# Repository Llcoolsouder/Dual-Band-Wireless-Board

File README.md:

# Dual-Band-Wireless-Board

This board is a proof of concept of a system which will allow seamless wireless data transfer and wireless power simultanneously; even when antennae are extremely close together.

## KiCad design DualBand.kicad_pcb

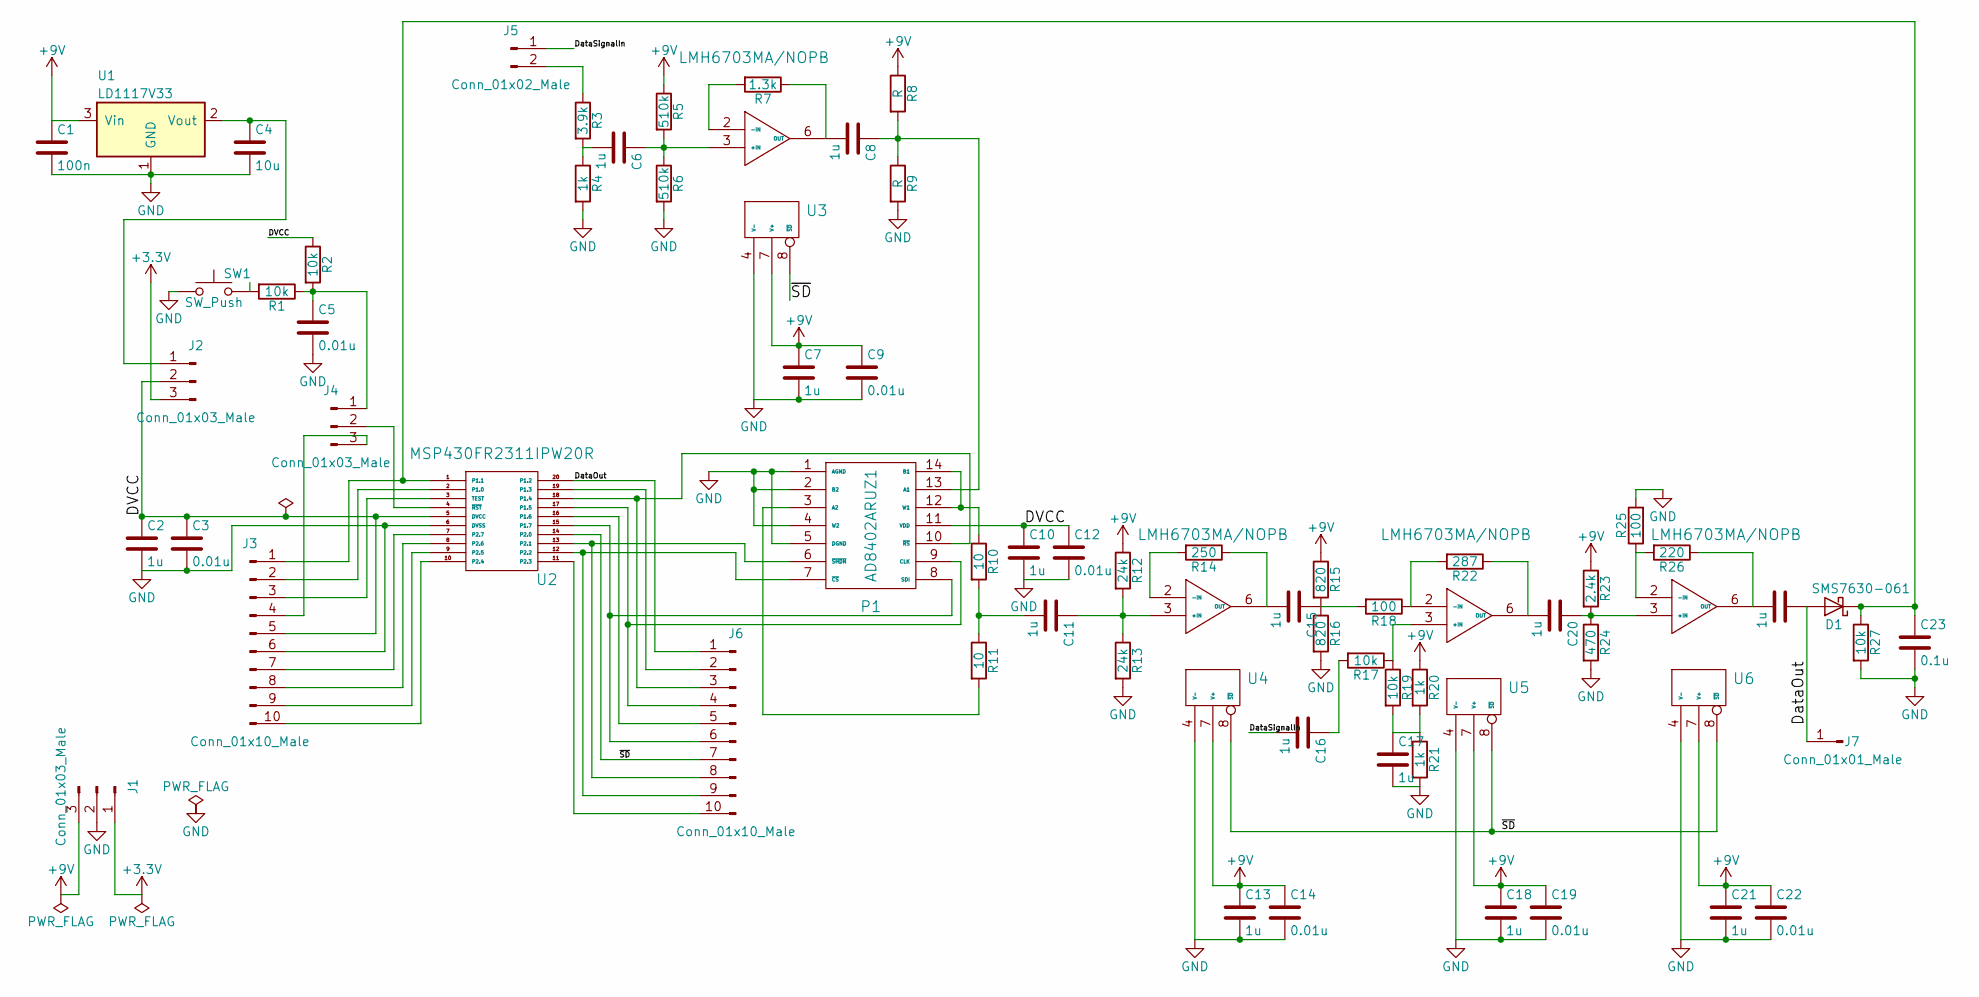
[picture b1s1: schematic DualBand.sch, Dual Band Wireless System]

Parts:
C1: 100n; C_0603
C2, C6, C7, C8, C10, C11, C13, C15, C16, C17, C18, C20, C21, C24: 1u; C_0603
C3, C5, C9, C12, C14, C19, C22: 0.01u; C_0603
C4: 10u; C_0603
C23: 0.1u; C_0603
D1: SMS7630-061; D_0201
J1, J2, J4: Conn_01x03_Male; Pin_Header_Straight_1x03_Pitch2.54mm
J3, J6: Conn_01x10_Male; Pin_Header_Straight_1x10_Pitch2.54mm
J5: Conn_01x02_Male; Pin_Header_Straight_1x02_Pitch2.54mm
J7: Conn_01x01_Male; Pin_Header_Straight_1x01_Pitch2.54mm
P1: AD8402ARUZ1; TSSOP-14_4.4x5mm_Pitch0.65mm
R1, R2, R17, R19, R27: 10k; R_0603
R3: 3.9k; R_0603
R4, R20, R21: 1k; R_0603
R5, R6: 510k; R_0603
R7: 1.3k; R_0603
R8, R9: R; R_0603
R10, R11: 10; R_0603
R12, R13: 24k; R_0603
R14: 250; R_0603
R15, R16: 820; R_0603
R18, R25: 100; R_0603
R22: 287; R_0603
R23: 2.4k; R_0603
R24: 470; R_0603
R26: 220; R_0603
SW1: SW_Push; FSM2JSMAATR
U1: LD1117V33; TO-220-3_Vertical
U2: MSP430FR2311IPW20R; TSSOP-20_4.4x6.5mm_Pitch0.65mm
U3, U4, U5, U6: LMH6703MA/NOPB; SOIC-8_3.9x4.9mm_Pitch1.27mm

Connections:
+3V3: J1.1, J2.3
+9V: C1.1, C7.1, C9.1, C13.1, C14.1, C18.1, C19.1, C21.1, C22.1, J1.3, R5.1, R8.1, R12.1, R15.1, R20.1, R23.1, U1.3 (Vin), U3.7 (V+), U4.7 (V+), U5.7 (V+), U6.7 (V+)
/DVCC: C2.1, C3.1, C10.1, C12.1, J2.2, J3.5, P1.11 (VDD), R2.1, U2.5 (DVCC)
/DataOut: C24.1, D1.2 (A), J6.1, J7.1, U2.20 (P1.2)
/DataSignalIn: C16.2, J5.1
/~SD: J6.7, U2.14 (P2.0), U3.8 (~SD), U4.8 (~SD), U5.8 (~SD), U6.8 (~SD)
GND: C1.2, C2.2, C3.2, C4.2, C5.2, C7.2, C9.2, C10.2, C12.2, C13.2, C14.2, C17.2, C18.2, C19.2, C21.2, C22.2, C23.2, J1.2, J3.6, P1.1 (AGND), P1.2 (B2), P1.4 (W2), P1.5 (DGND), R4.2, R6.2, R9.2, R13.2, R16.2, R21.2, R24.2, R25.2, R27.2, SW1.1, U1.1 (GND), U2.6 (DVSS), U3.4 (V-), U4.4 (V-), U5.4 (V-), U6.4 (V-)
unnamed: C4.1, J2.1, U1.2 (Vout)
unnamed: C5.1, J4.1, R1.1, R2.2
unnamed: C6.1, R5.2, R6.1, U3.3 (+IN)
unnamed: C6.2, R3.2, R4.1
unnamed: C8.1, P1.13 (A1), R8.2, R9.1
unnamed: C8.2, R7.1, U3.6 (OUT)
unnamed: C11.1, R12.2, R13.1, U4.3 (+IN)
unnamed: C11.2, R10.2, R11.1
unnamed: C15.1, R15.2, R16.1, R18.2
unnamed: C15.2, R14.1, U4.6 (OUT)
unnamed: C16.1, R17.2
unnamed: C17.1, R19.2, R20.2, R21.1
unnamed: C20.1, R23.2, R24.1, U6.3 (+IN)
unnamed: C20.2, R22.1, U5.6 (OUT)
unnamed: C23.1, D1.1 (K), J3.1, R27.1, U2.1 (P1.1)
unnamed: C24.2, R26.1, U6.6 (OUT)
unnamed: J3.2, U2.2 (P1.0)
unnamed: J3.3, U2.3 (TEST)
unnamed: J3.4, J4.3
unnamed: J3.7, U2.7 (P2.7)
unnamed: J3.8, U2.8 (P2.6)
unnamed: J3.9, U2.9 (P2.5)
unnamed: J3.10, U2.10 (P2.4)
unnamed: J4.2, U2.4 (~RST)
unnamed: J5.2, R3.1
unnamed: J6.2, U2.19 (P1.3)
unnamed: J6.3, P1.10 (~RS), U2.18 (P1.4)
unnamed: J6.4, P1.9 (CLK), U2.17 (P1.5)
unnamed: J6.5, U2.16 (P1.6)
unnamed: J6.6, P1.8 (SDI), U2.15 (P1.7)
unnamed: J6.8, P1.6 (~SHDN), U2.13 (P2.1)
unnamed: J6.9, P1.7 (~CS), U2.12 (P2.2)
unnamed: J6.10, U2.11 (P2.3)
unnamed: P1.3 (A2), R11.2
unnamed: P1.12 (W1), P1.14 (B1), R10.1
unnamed: R1.2, SW1.2
unnamed: R7.2, U3.2 (-IN)
unnamed: R14.2, U4.2 (-IN)
unnamed: R17.1, R19.1, U5.3 (+IN)
unnamed: R18.1, R22.2, U5.2 (-IN)
unnamed: R25.1, R26.2, U6.2 (-IN)

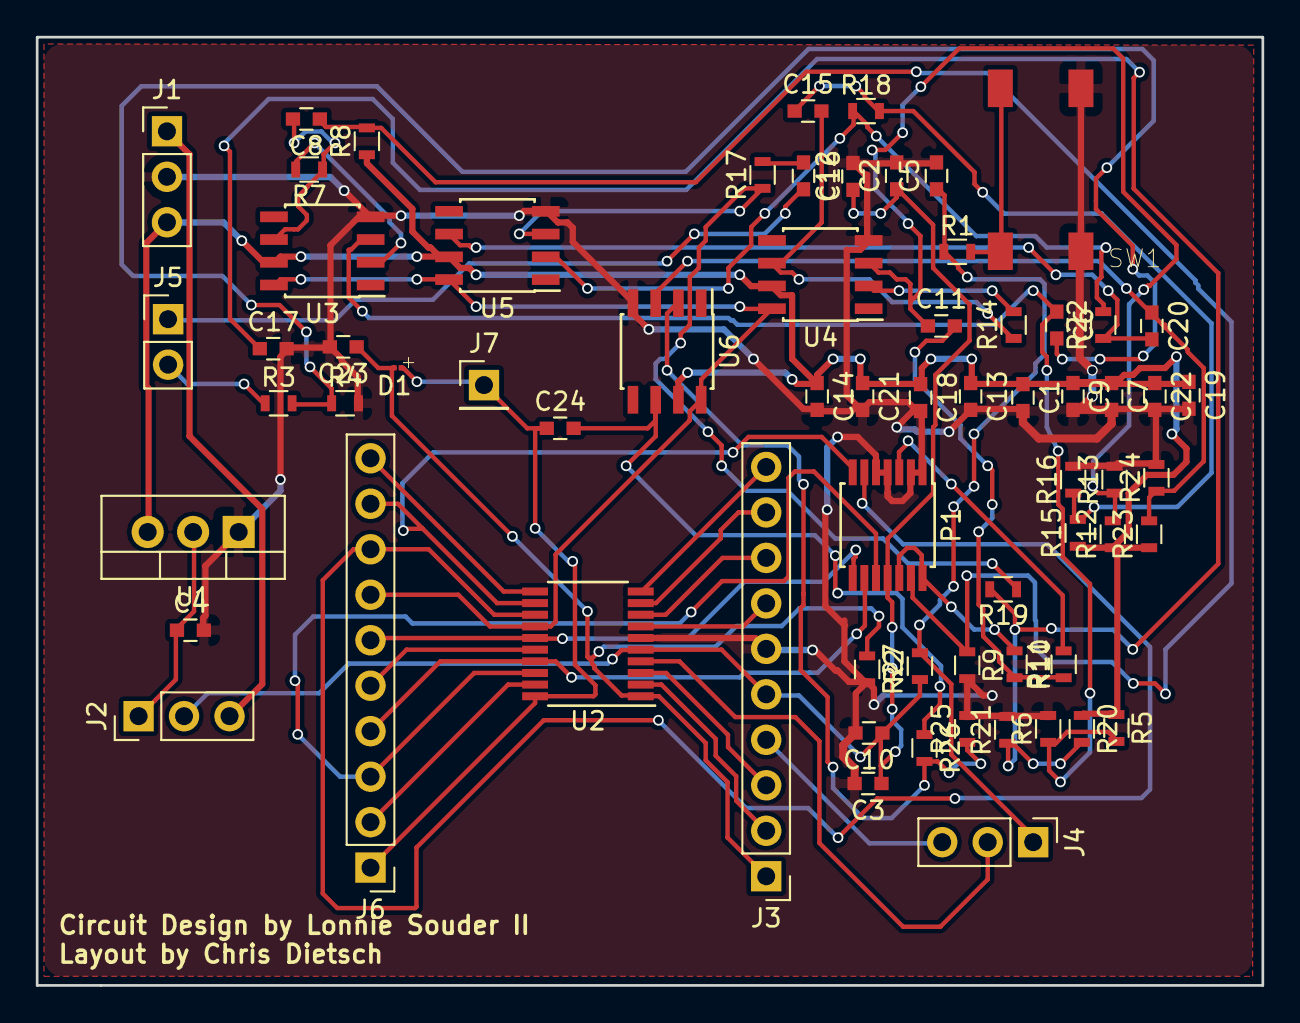
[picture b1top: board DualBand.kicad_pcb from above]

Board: 2 copper layers, 68.5 x 53.0 mm, 67 parts (0 on the bottom side), 48 nets.

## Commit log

2017-10-22 Created project
2017-10-22 Created README
2017-10-23 Connecting MCU
2017-10-23 Schematic almost finished. Needs headers and test points.
2017-10-25 Schematic finished. Need to select footprint for 2 more parts
2017-10-26 Selected footprints
2017-10-26 generated BOM
2017-10-27 fixed button footprint
2017-10-29 Creates the PCB layout; diode footprint messed up?
2017-10-31 Fixed the PCB edges so they're not enormous
2017-11-02 Finalizing some stuff
2017-11-02 Generated Gerbers
2017-11-03 Fixed board outline Gerber
2017-11-07 Added code for reading from ADC
2017-11-15 Fixed DC levels of amplifiers. Added 3.3V regulator
2017-11-18 Recreates PCB based on new layout
2017-11-18 Changed design rule to make DRC not whine about diode
2017-11-20 New gerbers
2017-11-28 Revised PCB
